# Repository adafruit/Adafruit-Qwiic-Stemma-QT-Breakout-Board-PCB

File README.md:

## Adafruit Qwiic / Stemma QT Breakout Board PCB

<a href="http://www.adafruit.com/products/5961"><br/>
Click here to purchase one from the Adafruit shop</a>

PCB files for the Adafruit Qwiic / Stemma QT Breakout Board. 

Format is EagleCAD schematic and board layout
* https://www.adafruit.com/product/5961

### Description

We got a request from a customer for a board that makes connecting between a breadboard and Stemma QT or Qwiic components easy, and here's what we whipped up!

The Adafruit Qwiic / Stemma QT Breakout Board is pretty simple: on one end is a JST SH-compatible connector, that will let you plug-and-play to the Qwiic or Stemma QT universe. On the other side is four 0.1" spaced pads where you can solder header or wires as you wish. In between are two 10K pullup resistors from the two I2C SDA/SCL lines to the positive power pin, plus a green ON LED so you know when the power pin and ground are properly wired.

And that's it! Simple but effective. You can use it both with 'I2C controllers' like a Feather, Metro, QT Py, or with 'I2C devices' like sensors, OLEDs or GPIO expanders. Since the lines just pass through, you can use it with 3 or 5V power and logic. The LED and pull-up resistors can be deactivated by cutting some small traces on the back of the PCB, if they are not needed.

### License

Adafruit invests time and resources providing this open source design, please support Adafruit and open-source hardware by purchasing products from [Adafruit](https://www.adafruit.com)!

Designed by Limor Fried/Ladyada for Adafruit Industries.

Creative Commons Attribution/Share-Alike, all text above must be included in any redistribution. 
See license.txt for additional details.

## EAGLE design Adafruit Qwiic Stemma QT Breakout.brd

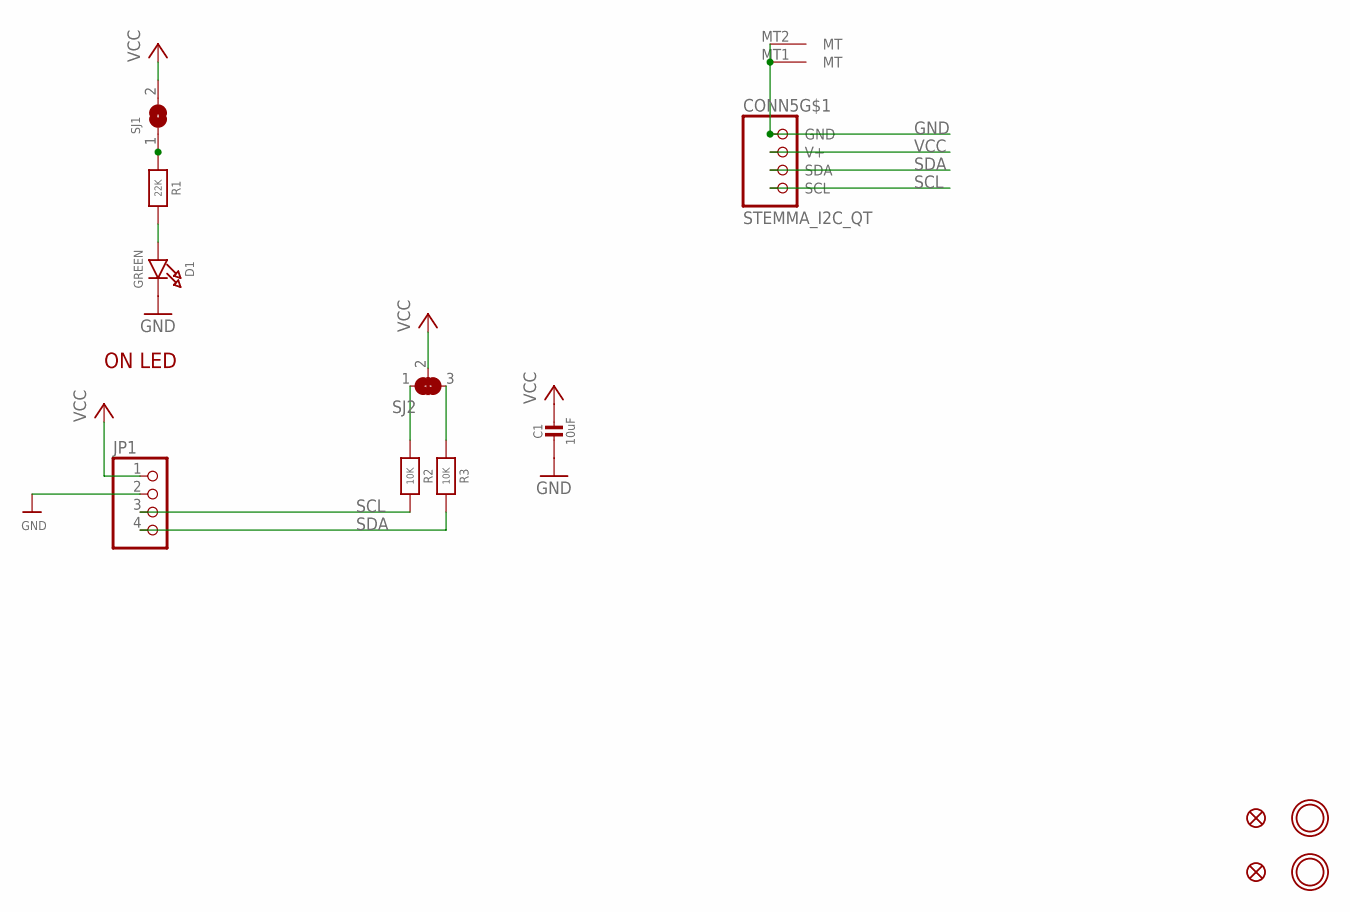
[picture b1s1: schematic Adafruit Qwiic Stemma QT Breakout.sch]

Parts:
C1: 10uF; 0805-NO
CONN5: STEMMA_I2C_QT; JST_SH4
D1: GREEN; CHIPLED_0603_NOOUTLINE
FID3, FID4: FIDUCIAL_1MM
JP1: HEADER-1X476MIL; 1X04_ROUND_76
R1: 22K; 0603-NO
R2, R3: 10K; 0603-NO
SJ1: SOLDERJUMPERCLOSED; SOLDERJUMPER_CLOSEDWIRE
SJ2: SOLDERJUMPER_2WAY; SOLDERJUMPER_2WAY_OPEN_NOPASTE
U$1, U$17: MOUNTINGHOLE2.5; MOUNTINGHOLE_2.5_PLATED

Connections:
GND: C1.2, CONN5.1 (GND), CONN5.MT1 (MT), CONN5.MT2 (MT), D1.C, JP1.2
unnamed: D1.A, R1.2
unnamed: R1.1, SJ1.1
unnamed: R2.1, SJ2.1
unnamed: R3.1, SJ2.3
SCL: CONN5.4 (SCL), JP1.3, R2.2
SDA: CONN5.3 (SDA), JP1.4, R3.2
VCC: C1.1, CONN5.2 (V+), JP1.1, SJ1.2, SJ2.2

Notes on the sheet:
ON LED

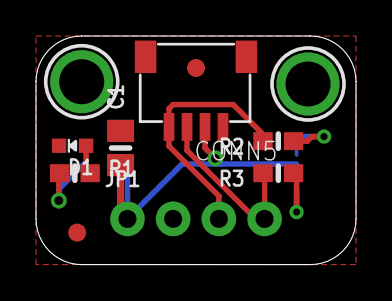
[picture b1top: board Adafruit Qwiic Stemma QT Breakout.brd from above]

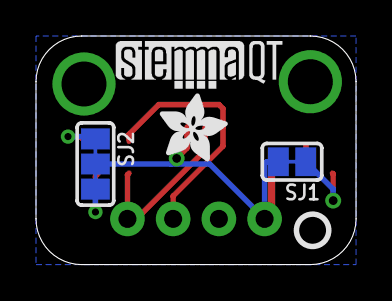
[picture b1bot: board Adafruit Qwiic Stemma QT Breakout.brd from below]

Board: 2 copper layers, 17.8 x 12.7 mm, 23 parts (7 on the bottom side), 8 nets.

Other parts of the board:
PLABEL0: PLABEL0
PLABEL1: PLABEL1
PLABEL2: PLABEL2
PLABEL3: PLABEL3
PLABEL4: PLABEL4
PLABEL5: PLABEL5
PLABEL6: PLABEL6
U$2: ADAFRUIT_3.5MM
U$25: PCBFEAT-REV-040
U$31: STEMMAQT

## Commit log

2024-05-08 cookiecutter

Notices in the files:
parts and their libraries:
microbuilder: This work is placed in the public domain, and may be freely used for commercial and non-commercial work with the following conditions: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
